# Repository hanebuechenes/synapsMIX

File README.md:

# synapsMIX — 4-Channel Analog VCA & Mixer (Eurorack)

**synapsMIX** is a compact, high-performance 4-channel analog VCA and summing sub-mixer for the Eurorack modular synth format.

## ⚡ Overview & Features

* **4 Independent VCAs:** Built around dual **LM13700** Operational Transconductance Amplifiers (OTAs) for linear CV response and clean signal amplification.

* **Low-Noise Master Summing:** Integrated summing bus routed through a **TL074** quad operational amplifier stage with manual output level control.

* **Per-Channel Visual Monitoring:**

  * **Audio In LEDs:** Antiparallel diode-protected (`1N4148W`) indicators for active signal detection on every channel.

  * **VCA Level LEDs:** Direct envelope/CV brightness feedback on each VCA control channel.

  * **Master Out LED:** Antiparallel-protected LED monitoring output audio level.

* **Eurorack Power Section:** Standard 10-pin power header with polarity protection, ferrite beads, and high/low-frequency decoupling capacitors.

## 🎛️ Signal Architecture

```
                               ┌─────────────────┐
[ Audio In 1 ] ──► [ VCA 1 ] ──┤                 │
[ Audio In 2 ] ──► [ VCA 2 ] ──┤  SUM_BUS (U3)   ├──► [ Master Vol ] ──► [ Master Out ]
[ Audio In 3 ] ──► [ VCA 3 ] ──┤ (TL074 Buffer)  │                           │
[ Audio In 4 ] ──► [ VCA 4 ] ──┤                 │                      (D11/D10 LED)
                               └─────────────────┘
      ▲                ▲
 [ CV In 1..4 ]   [ Trimmers ]

```

## 🛠️ Circuit Breakdown & Critical Design Notes

### 1. VCA & CV Control Stage (LM13700)

* **Control Input:** Accepts standard $+5\text{V}$ to $+10\text{V}$ envelopes/LFOs via `CVin1..4`.

* **CV LED Driver:** `D9` (and equivalents) tapped directly at `CVin` node with a $1\text{ k}\Omega$ current-limiting resistor (`R30`), returning to `GND`.

### 2. Audio Inputs & Antiparallel Indicators

* Audio input jacks feature antiparallel diode pairs (Standard LED + `1N4148W`) across the signal path to prevent reverse bias voltage breakdowns and visually reflect AC signal polarity.

### 3. Master Output & Buffer (TL074)

* Summed signals feed into `U3B` (TL074).

* The output path features an output protection resistor (`R28`, $1\text{ k}\Omega$) and an antiparallel-protected output LED (`D11` / `D10`).

* **Pin Orientation:** `D11` Anode points down to TL074 Output (Pin 7) via `R31`; Cathode connects to `GND`. `D10` (`1N4148W`) is placed antiparallel.

## 📄 License

This hardware design is released under the **MIT License**.

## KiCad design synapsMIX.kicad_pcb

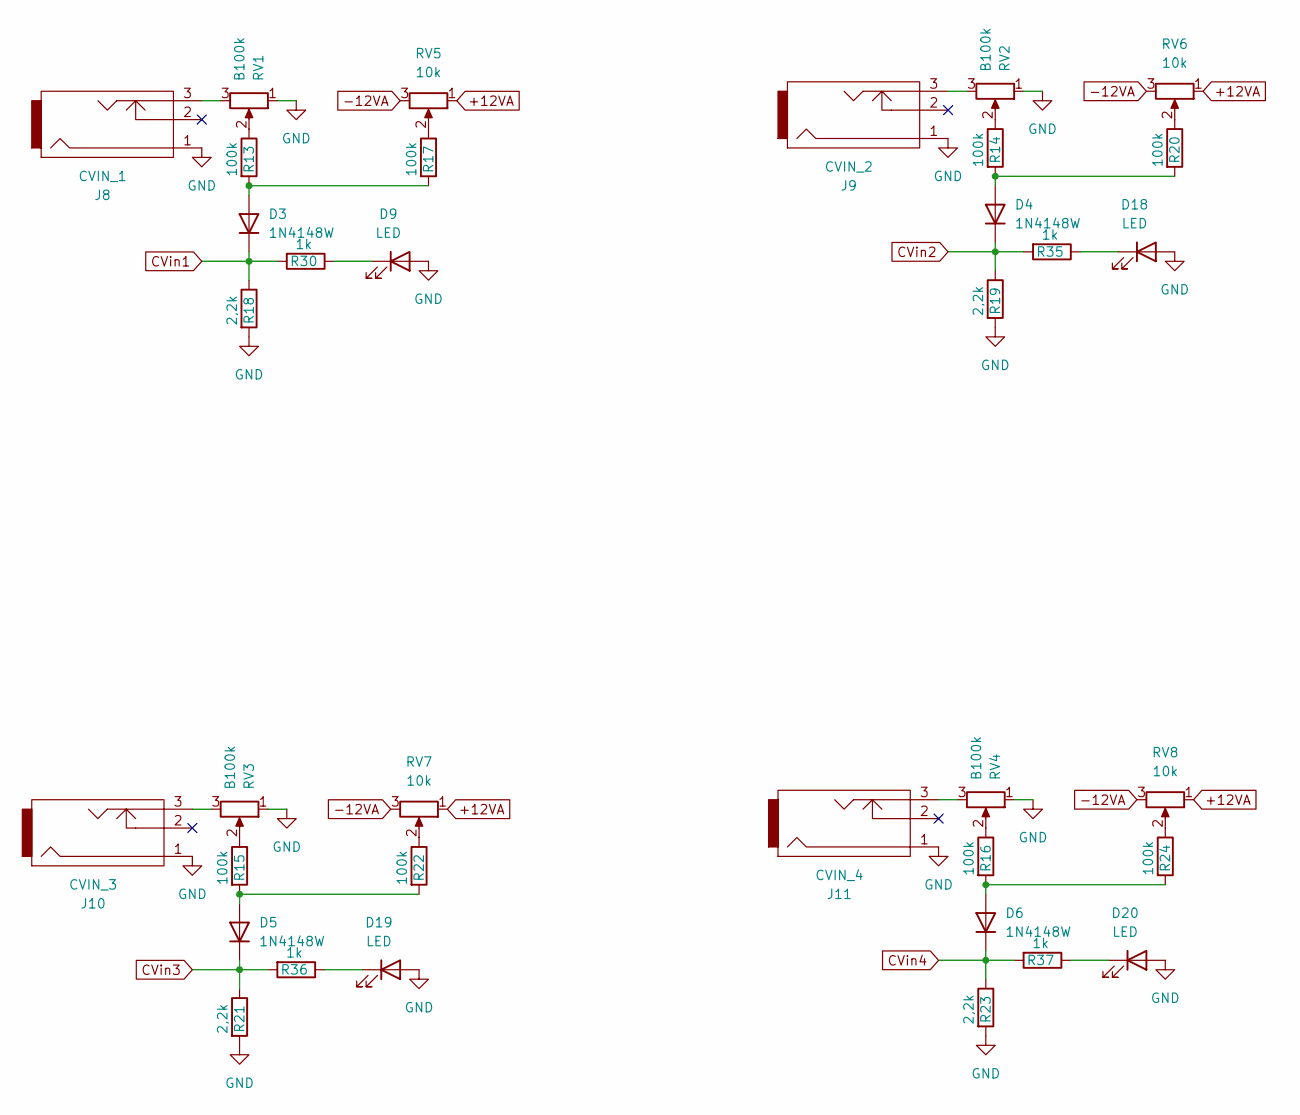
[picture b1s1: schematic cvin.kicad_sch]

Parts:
D3, D4, D5, D6: 1N4148W; D_SOD-123
D9, D18, D19, D20: LED; LED_D3.0mm_IRBlack
J8: CVIN_1; PJ301M-12; MFG Part Number WQP-WQP518MA; Digikey Part Number N/A
J9: CVIN_2; PJ301M-12; MFG Part Number WQP-WQP518MA; Digikey Part Number N/A
J10: CVIN_3; PJ301M-12; MFG Part Number WQP-WQP518MA; Digikey Part Number N/A
J11: CVIN_4; PJ301M-12; MFG Part Number WQP-WQP518MA; Digikey Part Number N/A
R13, R14, R15, R16, R17, R20, R22, R24: 100k; R_0603_1608Metric_Pad0.98x0.95mm_HandSolder
R18, R19, R21, R23: 2,2k; R_0603_1608Metric_Pad0.98x0.95mm_HandSolder
R30, R35, R36, R37: 1k; R_0603_1608Metric_Pad0.98x0.95mm_HandSolder
RV1, RV2, RV3, RV4: B100k; Potentiometer_Alps_RK09K_Single_Vertical
RV5, RV6, RV7, RV8: 10k; Potentiometer_Bourns_3296W_Vertical

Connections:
+12VA: RV5.1, RV6.1, RV7.1, RV8.1; also elsewhere on the board
-12VA: RV5.3, RV6.3, RV7.3, RV8.3; also elsewhere on the board
CVin1: D3.1 (K), R18.1, R30.2; also elsewhere on the board
CVin2: D4.1 (K), R19.1, R35.2
CVin3: D5.1 (K), R21.1, R36.2
CVin4: D6.1 (K), R23.1, R37.2
GND: D9.2 (A), D18.2 (A), D19.2 (A), D20.2 (A), J8.1, J9.1, J10.1, J11.1, R18.2, R19.2, R21.2, R23.2, RV1.1, RV2.1, RV3.1, RV4.1; also elsewhere on the board
unnamed: D3.2 (A), R13.2, R17.2
unnamed: D4.2 (A), R14.2, R20.2
unnamed: D5.2 (A), R15.2, R22.2
unnamed: D6.2 (A), R16.2, R24.2
unnamed: D9.1 (K), R30.1
unnamed: D18.1 (K), R35.1
unnamed: D19.1 (K), R36.1
unnamed: D20.1 (K), R37.1
unnamed: J8.3, RV1.3
unnamed: J9.3, RV2.3
unnamed: J10.3, RV3.3
unnamed: J11.3, RV4.3
unnamed: R13.1, RV1.2
unnamed: R14.1, RV2.2
unnamed: R15.1, RV3.2
unnamed: R16.1, RV4.2
unnamed: R17.1, RV5.2
unnamed: R20.1, RV6.2
unnamed: R22.1, RV7.2
unnamed: R24.1, RV8.2

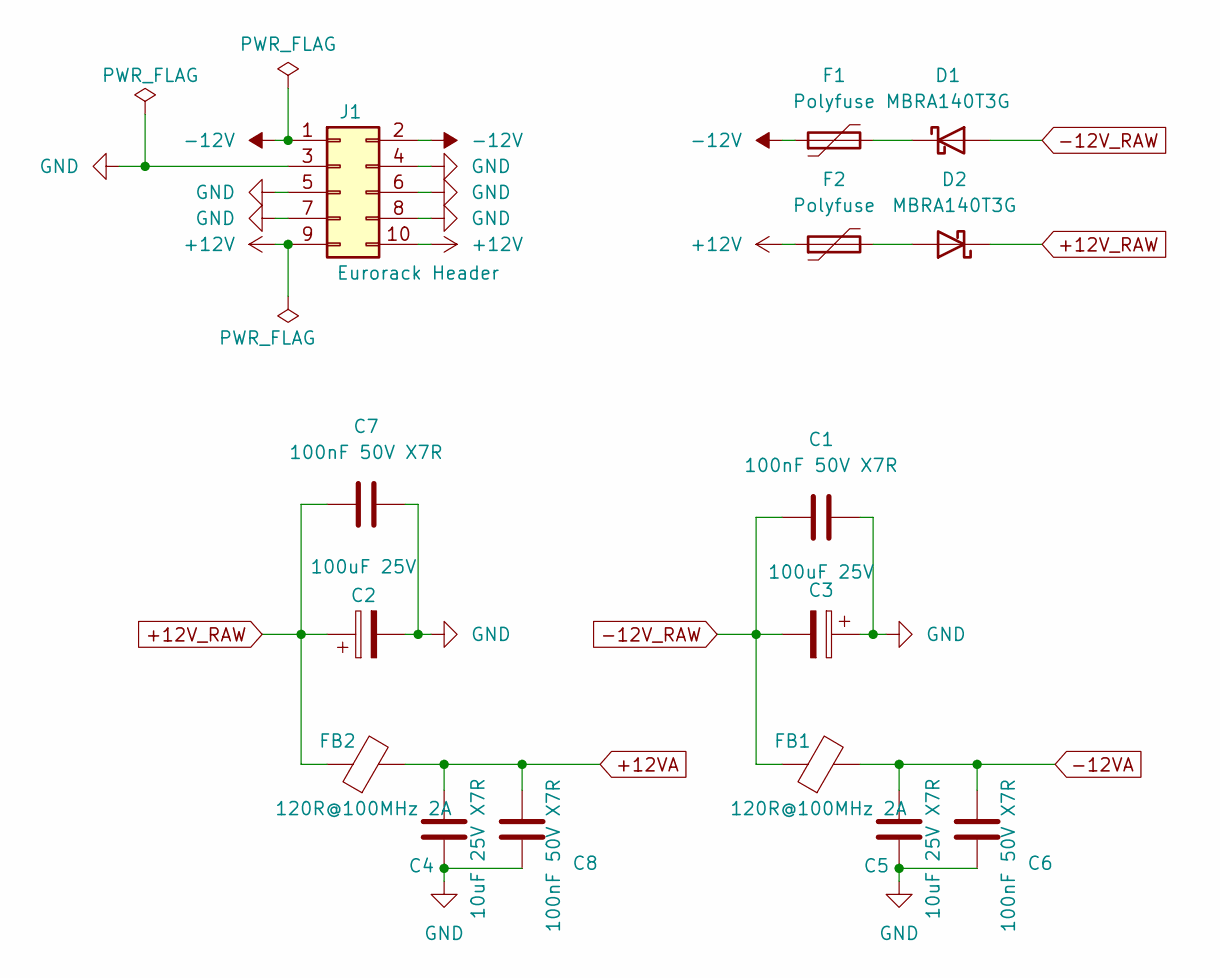
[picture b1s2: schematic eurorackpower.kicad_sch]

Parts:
C1, C6, C7, C8: 100nF 50V X7R; C_0603_1608Metric_Pad1.08x0.95mm_HandSolder
C2, C3: 100uF 25V; CP_Elec_6.3x7.7
C4, C5: 10uF 25V X7R; C_0805_2012Metric_Pad1.18x1.45mm_HandSolder
D1, D2: MBRA140T3G; D_SMA-SMB_Universal_Handsoldering
F1, F2: Polyfuse; Fuse_1210_3225Metric
FB1, FB2: 120R@100MHz 2A; L_0603_1608Metric_Pad1.05x0.95mm_HandSolder
J1: Eurorack Header; PinHeader_2x05_P2.54mm_Vertical

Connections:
+12V: F2.1, J1.9, J1.10
+12VA: C4.1, C8.1, FB2.2; also elsewhere on the board
+12V_RAW: C2.1, C7.1, D2.1 (K), FB2.1
-12V: F1.1, J1.1, J1.2
-12VA: C5.1, C6.1, FB1.2; also elsewhere on the board
-12V_RAW: C1.1, C3.2, D1.2 (A), FB1.1
GND: C1.2, C2.2, C3.1, C4.2, C5.2, C6.2, C7.2, C8.2, J1.3, J1.4, J1.5, J1.6, J1.7, J1.8; also elsewhere on the board
unnamed: D1.1 (K), F1.2
unnamed: D2.2 (A), F2.2

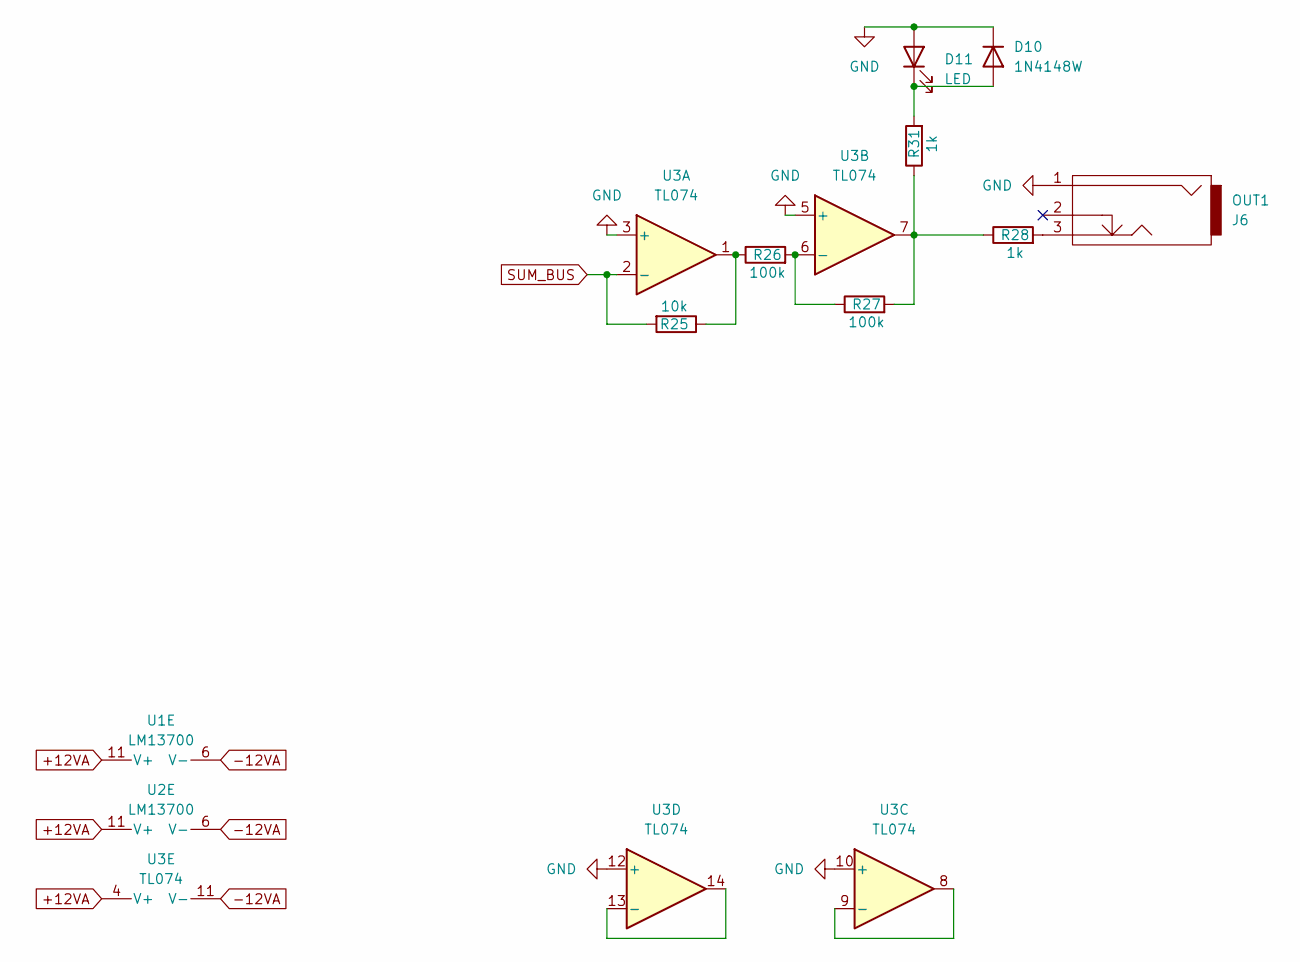
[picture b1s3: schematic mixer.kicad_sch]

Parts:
D10: 1N4148W; D_SOD-123
D11: LED; LED_D3.0mm_IRBlack
J6: OUT1; PJ301M-12; MFG Part Number WQP-WQP518MA; Digikey Part Number N/A
R25: 10k; R_0603_1608Metric_Pad0.98x0.95mm_HandSolder
R26, R27: 100k; R_0603_1608Metric_Pad0.98x0.95mm_HandSolder
R28, R31: 1k; R_0603_1608Metric_Pad0.98x0.95mm_HandSolder
U1, U2: LM13700; SOIC-16_3.9x9.9mm_P1.27mm
U3: TL074; SOIC-14_3.9x8.7mm_P1.27mm

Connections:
+12VA: U1.11 (V+), U2.11 (V+), U3.4 (V+); also elsewhere on the board
-12VA: U1.6 (V-), U2.6 (V-), U3.11 (V-); also elsewhere on the board
GND: D10.1 (K), D11.2 (A), J6.1, U3.3 (+), U3.5 (+), U3.10 (+), U3.12 (+); also elsewhere on the board
unnamed: D10.2 (A), D11.1 (K), R31.2
unnamed: J6.3, R28.2
unnamed: R25.1, R26.1, U3.1
unnamed: R27.2, R28.1, R31.1, U3.7
unnamed: R26.2, R27.1, U3.6 (-)
unnamed: U3.8, U3.9 (-)
unnamed: U3.13 (-), U3.14
SUM_BUS: R25.2, U3.2 (-); also elsewhere on the board

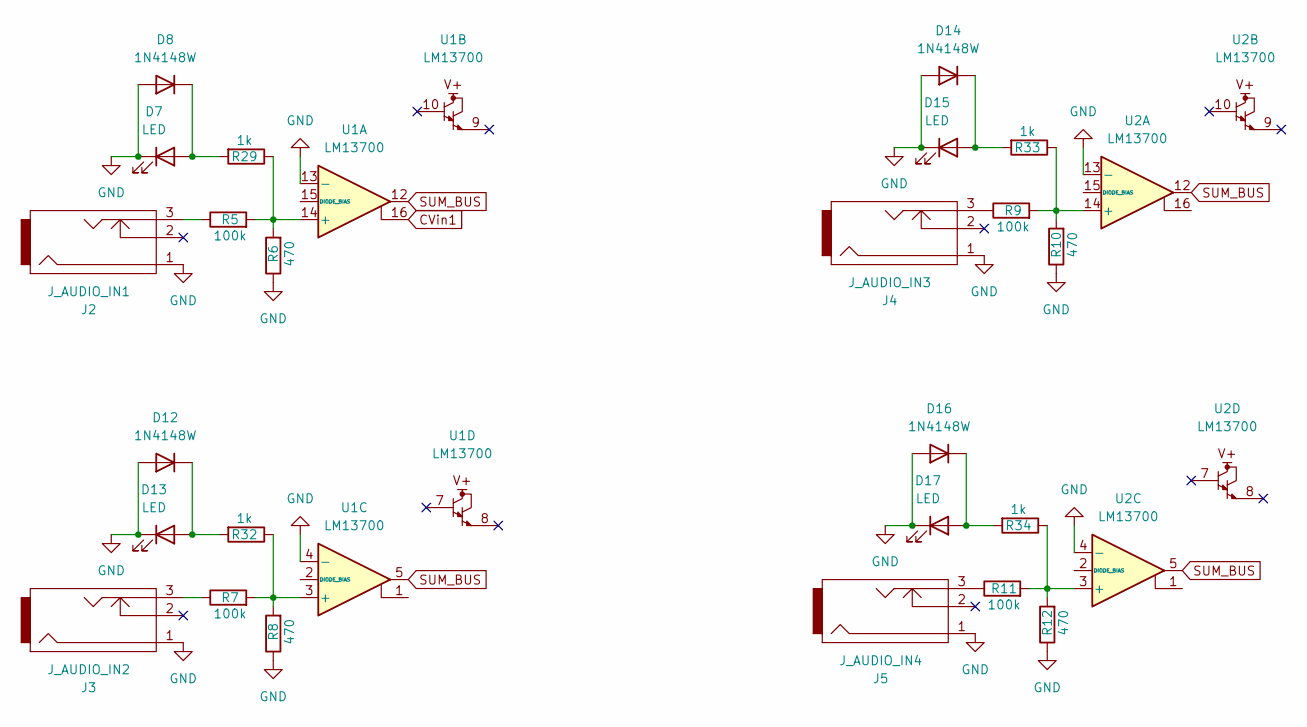
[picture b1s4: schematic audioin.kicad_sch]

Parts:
D7, D13, D15, D17: LED; LED_D3.0mm_IRBlack
D8, D12, D14, D16: 1N4148W; D_SOD-123
J2: J_AUDIO_IN1; PJ301M-12; MFG Part Number WQP-WQP518MA; Digikey Part Number N/A
J3: J_AUDIO_IN2; PJ301M-12; MFG Part Number WQP-WQP518MA; Digikey Part Number N/A
J4: J_AUDIO_IN3; PJ301M-12; MFG Part Number WQP-WQP518MA; Digikey Part Number N/A
J5: J_AUDIO_IN4; PJ301M-12; MFG Part Number WQP-WQP518MA; Digikey Part Number N/A
R5, R7, R9, R11: 100k; R_0603_1608Metric_Pad0.98x0.95mm_HandSolder
R6, R8, R10, R12: 470; R_0603_1608Metric_Pad0.98x0.95mm_HandSolder
R29, R32, R33, R34: 1k; R_0603_1608Metric_Pad0.98x0.95mm_HandSolder
U1, U2: LM13700; SOIC-16_3.9x9.9mm_P1.27mm

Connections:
CVin1: U1.16; also elsewhere on the board
GND: D7.1 (K), D8.2 (A), D12.2 (A), D13.1 (K), D14.2 (A), D15.1 (K), D16.2 (A), D17.1 (K), J2.1, J3.1, J4.1, J5.1, R6.1, R8.1, R10.1, R12.1, U1.4 (-), U1.13 (-), U2.4 (-), U2.13 (-); also elsewhere on the board
unnamed: D7.2 (A), D8.1 (K), R29.2
unnamed: D12.1 (K), D13.2 (A), R32.2
unnamed: D14.1 (K), D15.2 (A), R33.2
unnamed: D16.1 (K), D17.2 (A), R34.2
unnamed: J2.3, R5.1
unnamed: J3.3, R7.1
unnamed: J4.3, R9.1
unnamed: J5.3, R11.1
unnamed: R5.2, R6.2, R29.1, U1.14 (+)
unnamed: R7.2, R8.2, R32.1, U1.3 (+)
unnamed: R9.2, R10.2, R33.1, U2.14 (+)
unnamed: R11.2, R12.2, R34.1, U2.3 (+)
SUM_BUS: U1.5, U1.12, U2.5, U2.12; also elsewhere on the board

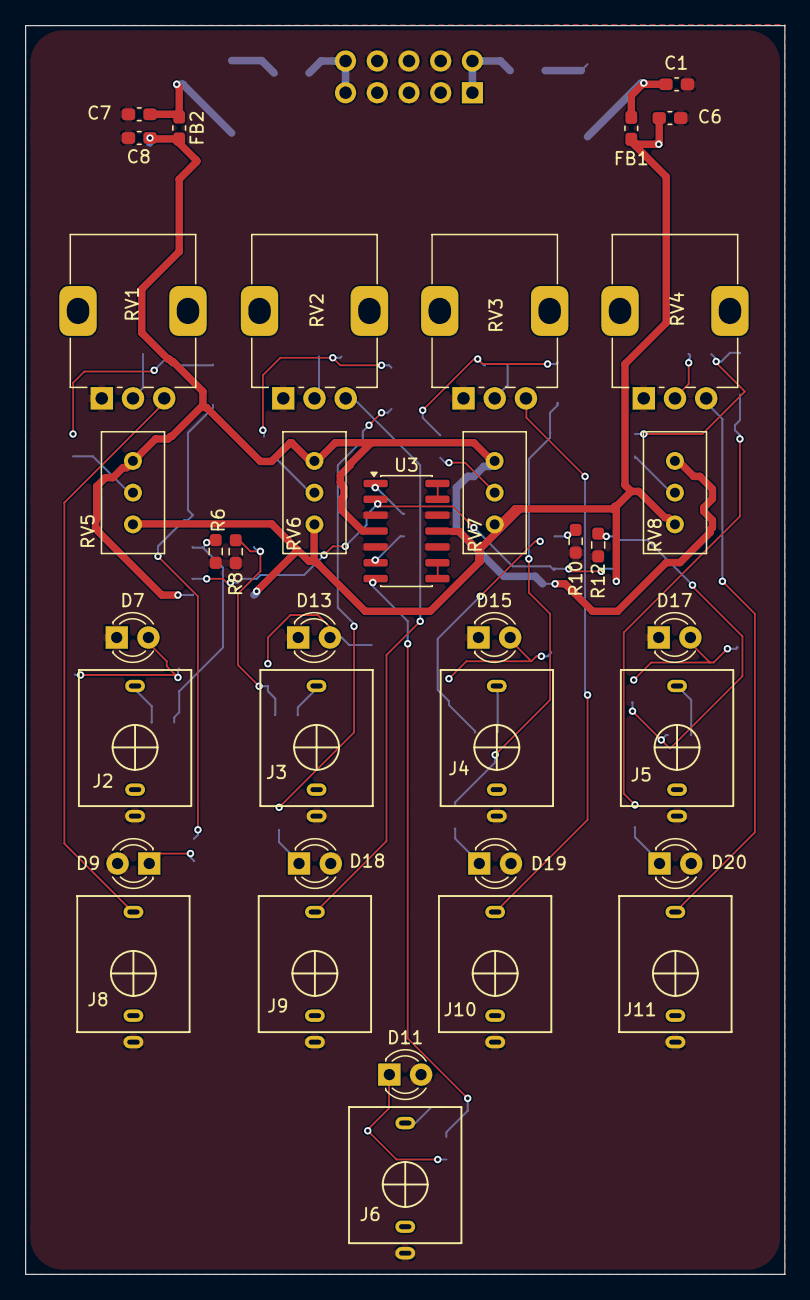
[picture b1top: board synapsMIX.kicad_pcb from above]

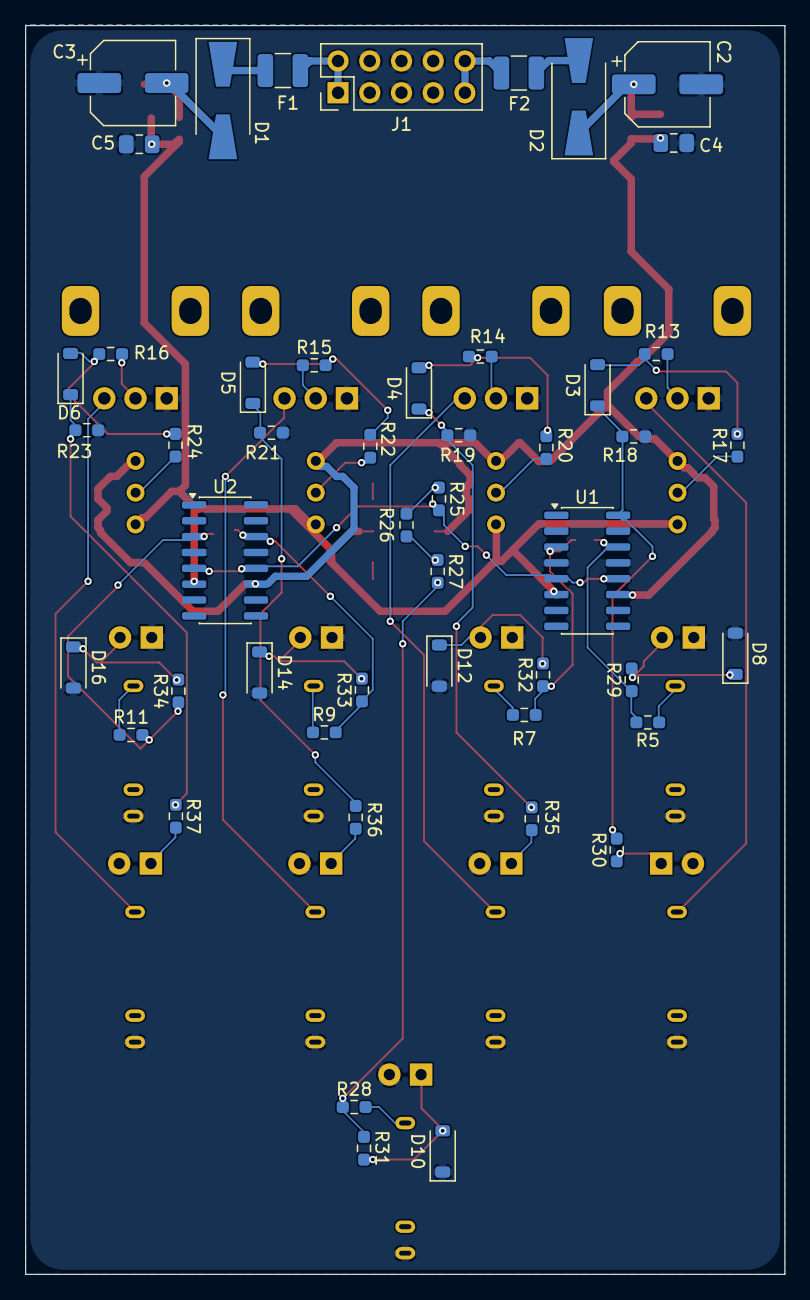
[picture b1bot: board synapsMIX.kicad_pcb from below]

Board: 2 copper layers, 60.8 x 100.0 mm, 86 parts (49 on the bottom side), 53 nets.

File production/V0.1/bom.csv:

Designator,Footprint,Quantity,Value,LCSC Part #
"C1, C6, C7, C8",0603,4,100nF 50V X7R,
"C2, C3",CP_Elec_6.3x7.7,2,100uF 25V,
"C4, C5",0805,2,10uF 25V X7R,
"D1, D2",D_SMA-SMB_Universal_Handsoldering,2,MBRA140T3G,
"D10, D12, D14, D16, D3, D4, D5, D6, D8",D_SOD-123,9,1N4148W,
"D11, D13, D15, D17, D18, D19, D20, D7, D9",LED_D3.0mm_IRBlack,9,LED,
"F1, F2",1210,2,Polyfuse,
"FB1, FB2",0603,2,120R@100MHz 2A,
J1,PinHeader_2x05_P2.54mm_Vertical,1,Eurorack Header,
J10,PJ301M-12,1,CVIN_3,
J11,PJ301M-12,1,CVIN_4,
J2,PJ301M-12,1,J_AUDIO_IN1,
J3,PJ301M-12,1,J_AUDIO_IN2,
J4,PJ301M-12,1,J_AUDIO_IN3,
J5,PJ301M-12,1,J_AUDIO_IN4,
J6,PJ301M-12,1,OUT1,
J8,PJ301M-12,1,CVIN_1,
J9,PJ301M-12,1,CVIN_2,
"R10, R12, R6, R8",0603,4,470,
"R11, R13, R14, R15, R16, R17, R20, R22, R24, R26, R27, R5, R7, R9",0603,14,100k,
"R18, R19, R21, R23",0603,4,"2,2k",
R25,0603,1,10k,
"R28, R29, R30, R31, R32, R33, R34, R35, R36, R37",0603,10,1k,
"RV1, RV2, RV3, RV4",Potentiometer_Alps_RK09K_Single_Vertical,4,B100k,
"RV5, RV6, RV7, RV8",Potentiometer_Bourns_3296W_Vertical,4,10k,
"U1, U2",SOIC-16_3.9x9.9mm_P1.27mm,2,LM13700,
U3,SOIC-14_3.9x8.7mm_P1.27mm,1,TL074,
